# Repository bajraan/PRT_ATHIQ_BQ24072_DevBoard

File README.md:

<!-- Begin README -->

<div align="center">

</div>
f
<p align="center">

    <br>
</p>

> [!NOTE]
> TODO:

> [!NOTE]
> **SW:**

<br><br><br><br>

<div align="center">
    
</div>

<!-- VARIANTS SECTION -->
<!-- VARIANTS SECTION -->
<!-- VARIANTS SECTION -->

<!-- GALLERY SECTION -->
<!-- GALLERY SECTION -->
<!-- GALLERY SECTION -->

---

<div align="center">

</div>

<!-- End README -->
<!-- github background #0d1117 -->

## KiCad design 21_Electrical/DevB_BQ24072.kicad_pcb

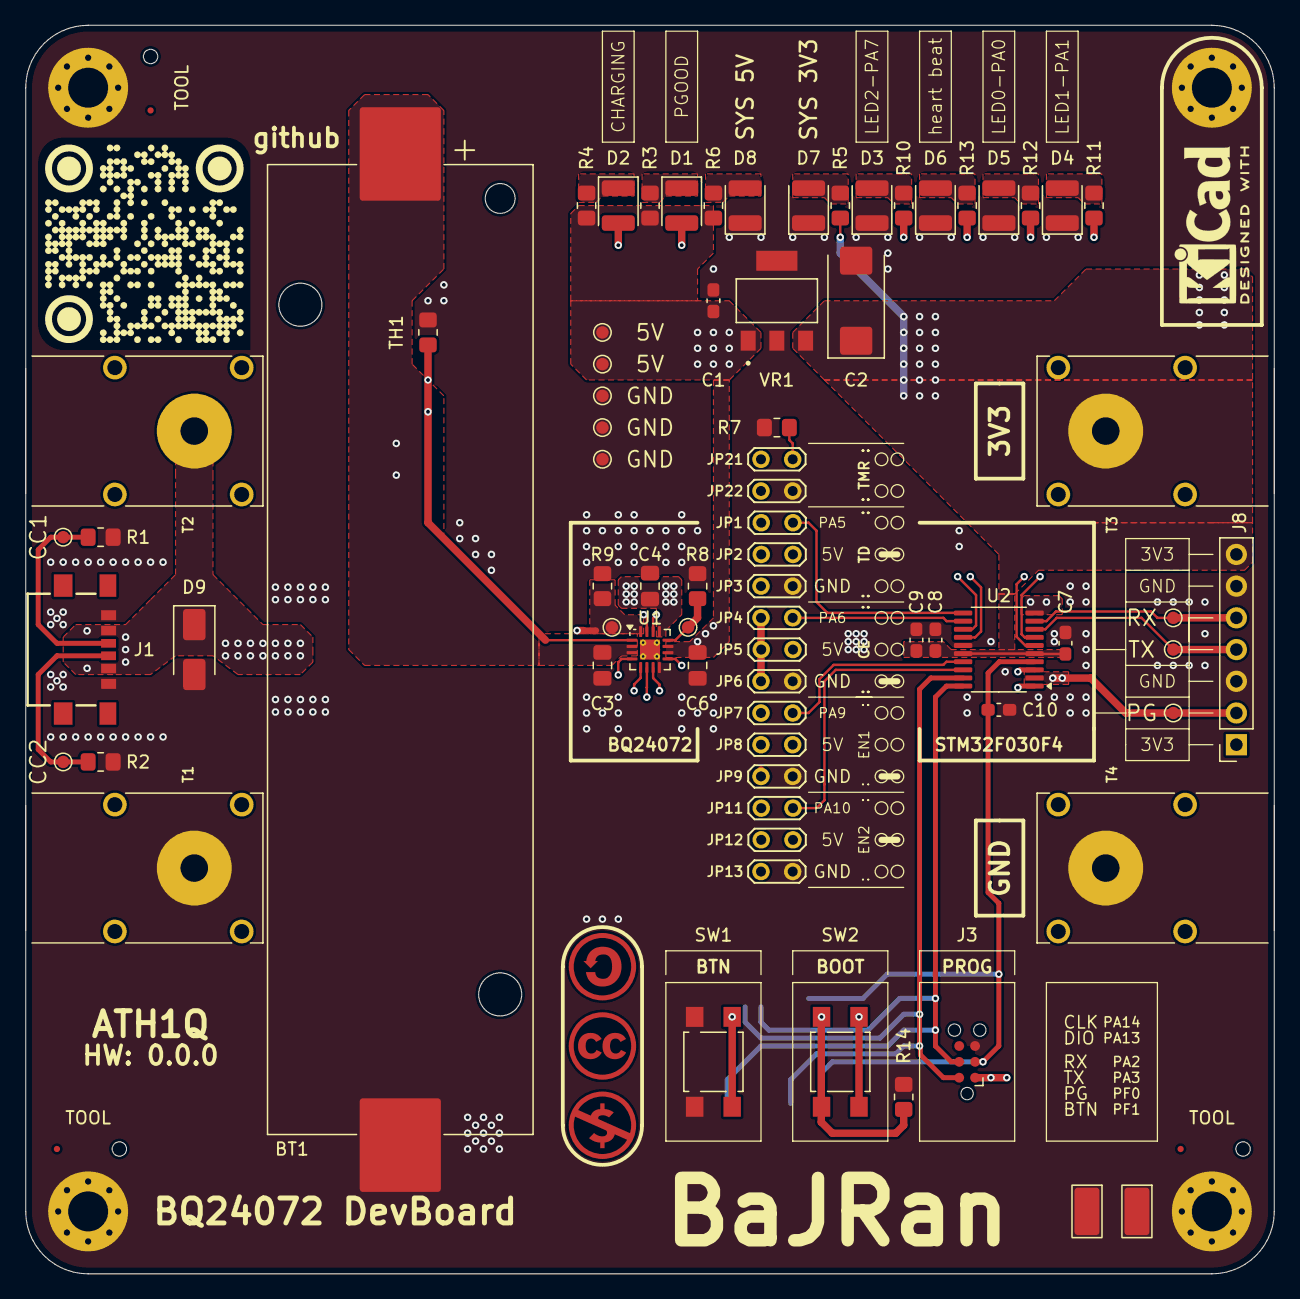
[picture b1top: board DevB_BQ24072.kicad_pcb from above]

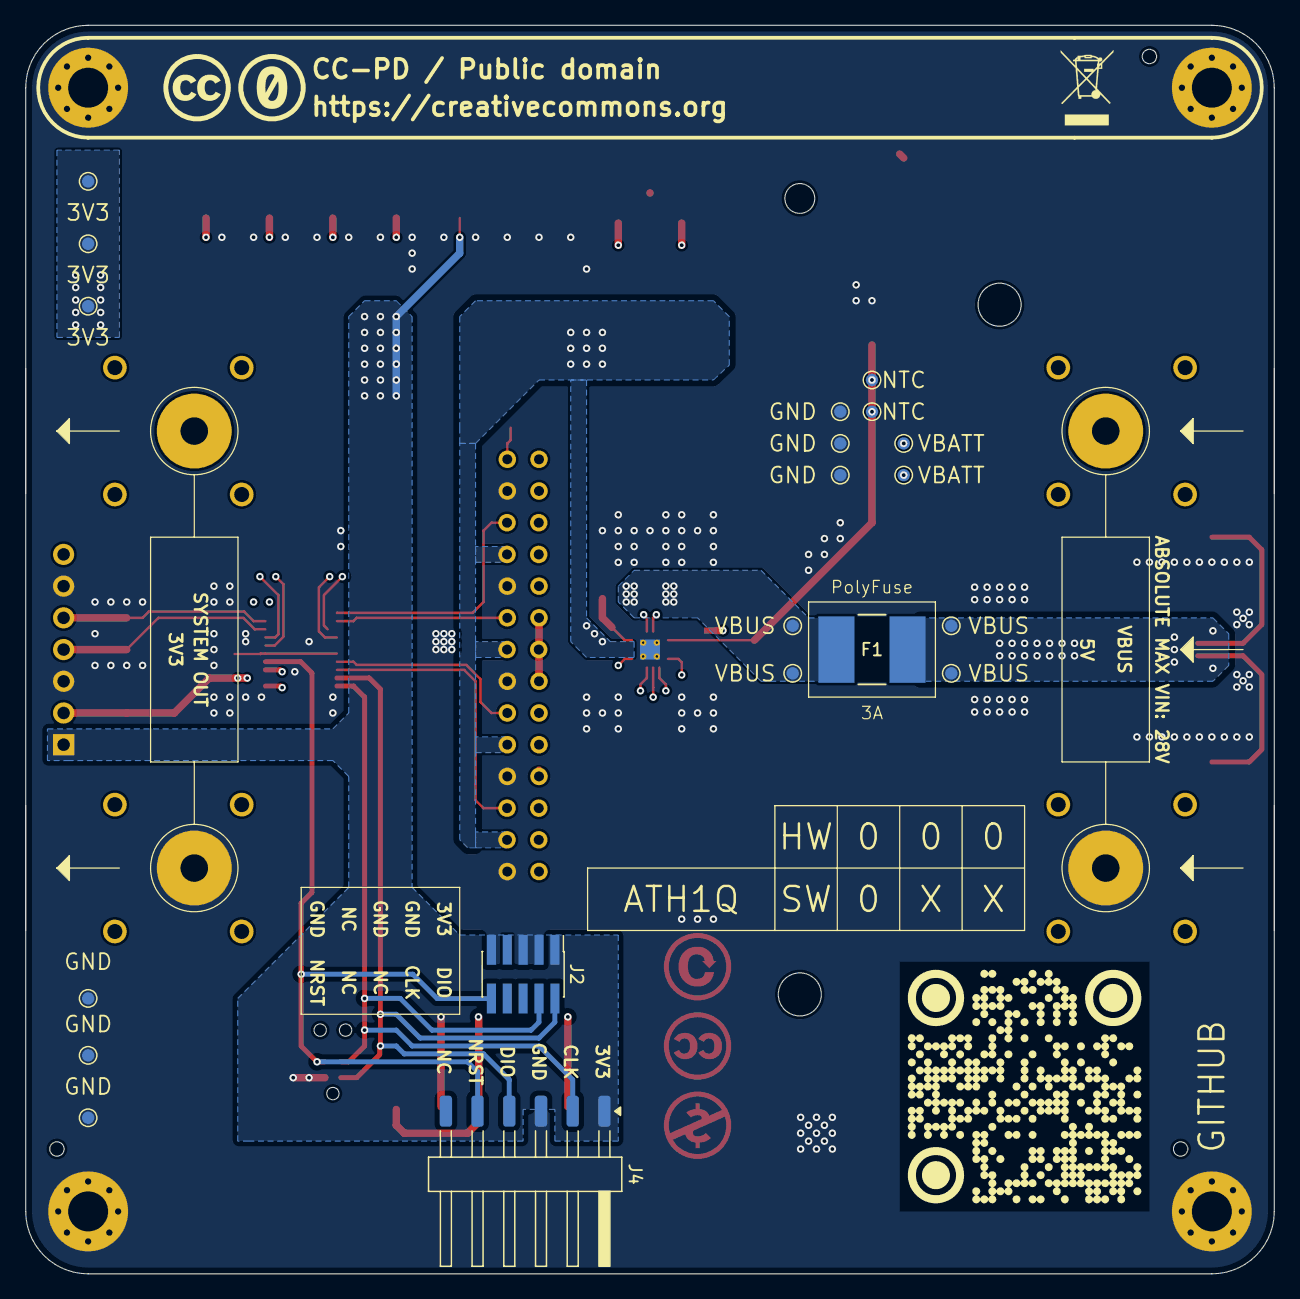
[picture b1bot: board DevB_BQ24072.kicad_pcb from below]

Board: 4 copper layers, 100.0 x 100.0 mm, 105 parts (20 on the bottom side), 43 nets.

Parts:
BT1: 18650; BatteryHolder_Keystone_1042_1x18650
C1, C9: 1u/50V; C_0603_1608Metric_Pad1.08x0.95mm_HandSolder
C2: 47u/16V; CP_EIA-7343-31_Kemet-D_HandSolder
C3, C4, C6: 4u7/35V; C_0805_2012Metric_Pad1.18x1.45mm_HandSolder
C7, C8, C10: 100n/50V; C_0603_1608Metric_Pad1.08x0.95mm_HandSolder
D1, D2, D3, D4, D5, D6, D7, D8: LED_Small_Filled; LED_1210_3225Metric
D9: SMAJ24A; D_SMA
F1: 2920L330/24MR; FUSE_2920L330_24MR_LTF
FID1, FID2, FID3: Fiducial; Fiducial_0.5mm_Mask1mm
H1, H2, H3, H4: MountingHole_Pad; MountingHole_3.2mm_M3_Pad_Via
H5, H6, H7: MountingHole_Pad; ToolingHole_1.152mm
J1: USB4135-GF-A_REVA; GCT_USB4135-GF-A_REVA
J2: Conn_ARM_JTAG_SWD_10; PinHeader_2x05_P1.27mm_Vertical_SMD
J3: SWD1; Tag-Connect_TC2030-IDC-NL_2x03_P1.27mm_Vertical
J4: Conn_01x06_Pin; Harwin_M20-89006xx_1x06_P2.54mm_Horizontal
J8: Conn_01x07_Pin; PinSocket_1x07_P2.54mm_Vertical
JP1, JP2, JP3, JP4, JP5, JP6, JP7, JP8, JP9, JP11, JP12, JP13, JP21, JP22: Jumper_2_Open; TestPoint_2Pads_Pitch2.54mm_Drill0.8mm
NT2: NetTie_2; NetTie-2_SMD_Pad0.5mm
R1, R2: 5k1; R_0805_2012Metric_Pad1.20x1.40mm_HandSolder
R3, R4, R10, R11, R12, R13: 1k; R_0805_2012Metric_Pad1.20x1.40mm_HandSolder
R5: 200; R_0805_2012Metric_Pad1.20x1.40mm_HandSolder
R6: 370; R_0805_2012Metric_Pad1.20x1.40mm_HandSolder
R7: XX; R_0805_2012Metric_Pad1.20x1.40mm_HandSolder
R8: 1k15; R_0805_2012Metric_Pad1.20x1.40mm_HandSolder
R9: 0k65; R_0805_2012Metric_Pad1.20x1.40mm_HandSolder
R14: 10k; R_0805_2012Metric_Pad1.20x1.40mm_HandSolder
SW1: BTN; SW_SPST_TL3305A
SW2: BOOT0; SW_SPST_TL3305A
T1, T2, T3, T4: SWEB_8094; SWEB_8094_GE
TH1: 10k; R_0805_2012Metric_Pad1.20x1.40mm_HandSolder
TP1: CC1; TestPoint_Pad_D1.0mm
TP2: CC2; TestPoint_Pad_D1.0mm
TP3, TP11, TP12, TP13, TP20, TP24, TP25, TP26, TP27: GND; TestPoint_Pad_D1.0mm
TP4, TP5, TP28, TP29: VBUS; TestPoint_Pad_D1.0mm
TP6, TP7: 5V; TestPoint_Pad_D1.0mm
TP8, TP9, TP10: 3V3; TestPoint_Pad_D1.0mm
TP14: ilim; TestPoint_Pad_D1.0mm
TP15: iset; TestPoint_Pad_D1.0mm
TP16, TP17: VBATT; TestPoint_Pad_D1.0mm
TP18, TP19: NTC; TestPoint_Pad_D1.0mm
TP21: PG; TestPoint_Pad_D1.0mm
TP22: RX; TestPoint_Pad_D1.0mm
TP23: TX; TestPoint_Pad_D1.0mm
TP31: GND; TestPoint_Keystone_5019_Miniature
TP32: TestPoint; TestPoint_Keystone_5019_Miniature
U1: BQ24072RGT; VQFN-16-1EP_3x3mm_P0.5mm_EP1.6x1.6mm_ThermalVias
U2: STM32F030F4Px; TSSOP-20_4.4x6.5mm_P0.65mm
VR1: TS2940CW33_RPG

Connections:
/BAT_NTC: TH1.1, TP18.1, TP19.1, U1.1 (TS)
/BAT_V: BT1.1 (+), C3.1, TP16.1, TP17.1, U1.2 (BAT), U1.3 (BAT)
/BQ_ilim: R8.1, TP14.1, U1.12 (ILIM)
/BQ_iset: NT2.1, R9.1, TP15.1, U1.16 (ISET)
/BQ_tmr: JP21.1 (A), JP22.1 (A), U1.14 (TMR)
/BTN: SW1.2, U2.3 (PF1)
/BTN_boot: R14.1, SW2.2, U2.1 (BOOT0)
/CFG_CE: JP4.1 (A), JP5.1 (A), JP6.1 (A), U1.4 (~CE)
/CFG_EN1: JP7.1 (A), JP8.1 (A), JP9.1 (A), U1.6 (EN1)
/CFG_EN2: JP11.1 (A), JP12.1 (A), JP13.1 (A), U1.5 (EN2)
/CFG_TD: JP1.1 (A), JP2.1 (A), JP3.1 (A), U1.15 (TD)
/LED_0: R12.1, U2.6 (PA0)
/LED_1: R11.1, U2.7 (PA1)
/LED_2: R10.1, U2.13 (PA7)
/LED_3V3: D7.2 (A), R5.2
/LED_5V: D8.2 (A), R6.2
/LED_10: D5.2 (A), R12.2
/LED_11: D4.2 (A), R11.2
/LED_12: D3.2 (A), R10.2
/LED_PG: D2.2 (A), J8.2, TP21.1, U1.7 (~PGOOD), U2.2 (PF0)
/LED_PG1: D2.1 (K), R4.1
/LED_hG: D1.2 (A), U1.9 (~CHG)
/LED_hG1: D1.1 (K), R3.1
/LED_heartBeat: R13.1, U2.14 (PB1)
/PWR_SYS_3V3: C2.1, C7.1, C8.1, C9.1, J2.1 (VTref), J3.1 (VCC), J4.1, J8.1, J8.7, R5.1, SW2.1, T3.1, TP8.1, TP9.1, TP10.1, U2.5 (VDDA), U2.16 (VDD), VR1.3 (OUT)
/PWR_SYS_5V: C1.1, C6.1, JP2.2 (B), JP5.2 (B), JP8.2 (B), JP12.2 (B), R3.2, R4.2, R6.1, TP6.1, TP7.1, U1.10 (OUT), U1.11 (OUT), VR1.1 (IN)
/PWR_VBUS: D9.1 (A1), F1.1, J1.A9 (VBUS_A), J1.B9 (VBUS_B), T2.1, TP4.1, TP5.1
/PWR_VBUS_F: C4.1, F1.2, TP28.1, TP29.1, U1.13 (IN)
/STM_CE: JP4.2 (B), U2.12 (PA6)
/STM_EN1: JP7.2 (B), U2.17 (PA9)
/STM_EN2: JP11.2 (B), U2.18 (PA10)
/STM_TD: JP1.2 (B), U2.11 (PA5)
/STM_isense: NT2.2, U2.10 (PA4)
/SW_CLK: J2.4 (SWCLK/TCK), J3.4 (SWCLK), J4.2, U2.20 (PA14)
/SW_DIO: J2.2 (SWDIO/TMS), J3.2 (SWDIO), J4.4, U2.19 (PA13)
/SW_NRST: C10.1, J2.10 (~RESET), J3.3 (~RESET), J4.5, U2.4 (NRST)
/USART_RX: J8.5, TP22.1, U2.9 (PA3)
/USART_TX: J8.4, TP23.1, U2.8 (PA2)
/USB_CC1: J1.A5 (CC1), R1.1, TP1.1
/USB_CC2: J1.B5 (CC2), R2.1, TP2.1
GND: BT1.2 (-), C1.2, C2.2, C3.2, C4.2, C6.2, C7.2, C8.2, C9.2, C10.2, D3.1 (K), D4.1 (K), D5.1 (K), D6.1 (K), D7.1 (K), D8.1 (K), D9.2 (A2), H1.1, H2.1, H3.1, H4.1, J1.A12 (GND_A), J1.B12 (GND_B), J2.3 (GND), J2.5 (GND), J2.9 (GNDDetect), J3.5 (GND), J4.3, J8.3, J8.6, JP3.2 (B), JP6.2 (B), JP9.2 (B), JP13.2 (B), JP22.2 (B), R1.2, R2.2, R7.1, R8.2, R9.2, R14.2, SW1.1, T1.1, T4.1, TH1.2, TP3.1, TP11.1, TP12.1, TP13.1, TP20.1, TP24.1, TP25.1, TP26.1, TP27.1, TP31.1, TP32.1, U1.8 (VSS), U1.17 (VSS), U2.15 (VSS), VR1.2 (GND), VR1.4 (GND)
unnamed: D6.2 (A), R13.2
unnamed: JP21.2 (B), R7.2

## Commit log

2025-06-10 .gitignore deployed
2025-06-12 PCB added SWD programateor connectors, README.MD update
2025-06-12 readme.md small touches

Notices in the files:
parts and their libraries:
CC-PD / Public domain
